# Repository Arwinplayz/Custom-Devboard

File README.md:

# Custom Devboard
A custom Devboard inspired by the Pico made in kicad
---

## Project Overview
The goal was to create a custom devboard PCB within kicad and learn how they truely work in the process.

This was one of my first projects I did so I truely learnt alot from it. Took some time off due to school and exams but finally managed to fint time to finish. Its multipurpose and fully programable GPIO pins so I look forward to using it alonside some other projects in the future. I decided overall to make this project because it would give me something really useful for future creations. Before this I had not a clue how microcontrollers and devboards worked but now I know so much.

---

## Screenshots

### 1. Overall

### 2. Schematic

### 3. PCB layout

### 4. Design

### Bill Of Materials

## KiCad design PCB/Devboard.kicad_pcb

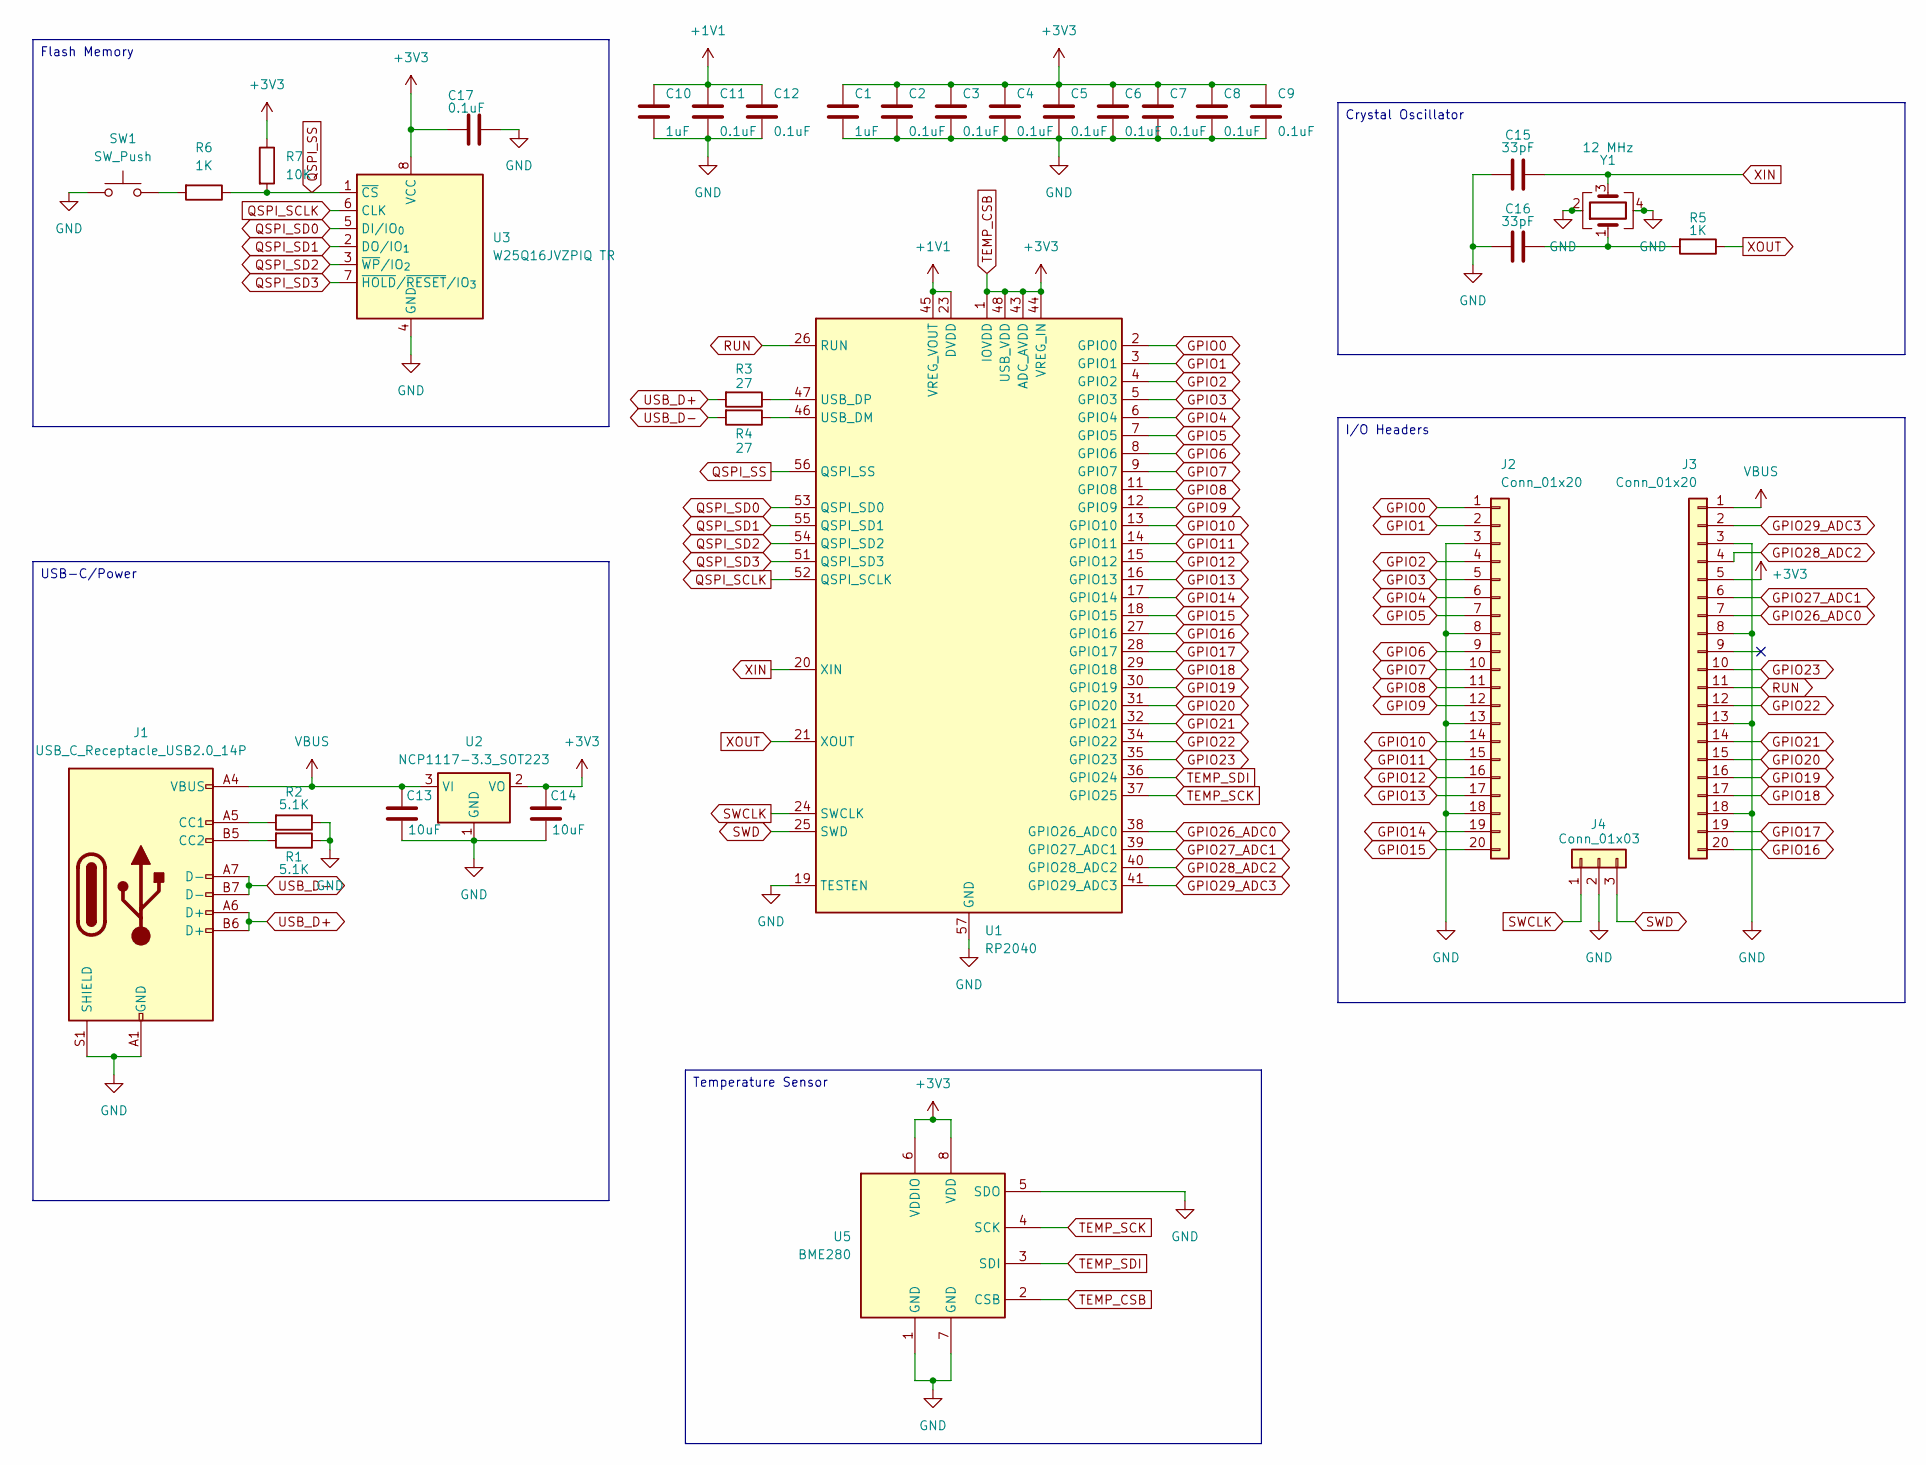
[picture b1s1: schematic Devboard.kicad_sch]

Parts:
C1, C10: 1uF; C_0402_1005Metric
C2, C3, C4, C5, C6, C7, C8, C9, C11, C12, C17: 0.1uF; C_0402_1005Metric
C13, C14: 10uF; C_0603_1608Metric
C15, C16: 33pF; C_0402_1005Metric
J1: USB_C_Receptacle_USB2.0_14P; USB_C_Receptacle_HRO_TYPE-C-31-M-12
J2, J3: Conn_01x20; PinHeader_1x20_P2.54mm_Vertical
J4: Conn_01x03; PinHeader_1x03_P2.54mm_Vertical
R1, R2: 5.1K; R_0402_1005Metric
R3, R4: 27; R_0402_1005Metric
R5, R6: 1K; R_0402_1005Metric
R7: 10K; R_0402_1005Metric
SW1: SW_Push; SW_Push_SPST_NO_Alps_SKRK
U1: RP2040; QFN-56-1EP_7x7mm_P0.4mm_EP3.2x3.2mm
U2: NCP1117-3.3_SOT223; SOT-23
U3: W25Q16JVZPIQ TR; Winbond_USON-8-1EP_3x2mm_P0.5mm_EP0.2x1.6mm
U5: BME280; Bosch_LGA-8_2.5x2.5mm_P0.65mm_ClockwisePinNumbering
Y1: 12 MHz; Crystal_SMD_3225-4Pin_3.2x2.5mm

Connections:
+1V1: C10.1, C11.1, C12.1, U1.23 (DVDD), U1.45 (VREG_VOUT), U1.50 (DVDD)
GND: C1.2, C2.2, C3.2, C4.2, C5.2, C6.2, C7.2, C8.2, C9.2, C10.2, C11.2, C12.2, C13.2, C14.2, C15.2, C16.2, C17.1, J1.A1 (GND), J1.A12 (GND), J1.B1 (GND), J1.B12 (GND), J1.S1 (SHIELD), J2.3, J2.8, J2.13, J2.18, J3.3, J3.8, J3.13, J3.18, J4.2, R1.1, R2.1, SW1.1, U1.19 (TESTEN), U1.57 (GND), U2.1 (GND), U3.4 (GND), U5.1 (GND), U5.5 (SDO), U5.7 (GND), Y1.2, Y1.4
GPIO0: J2.1, U1.2 (GPIO0)
GPIO1: J2.2, U1.3 (GPIO1)
GPIO2: J2.4, U1.4 (GPIO2)
GPIO3: J2.5, U1.5 (GPIO3)
GPIO4: J2.6, U1.6 (GPIO4)
GPIO5: J2.7, U1.7 (GPIO5)
GPIO6: J2.9, U1.8 (GPIO6)
GPIO7: J2.10, U1.9 (GPIO7)
GPIO8: J2.11, U1.11 (GPIO8)
GPIO9: J2.12, U1.12 (GPIO9)
GPIO10: J2.14, U1.13 (GPIO10)
GPIO11: J2.15, U1.14 (GPIO11)
GPIO12: J2.16, U1.15 (GPIO12)
GPIO13: J2.17, U1.16 (GPIO13)
GPIO14: J2.19, U1.17 (GPIO14)
GPIO15: J2.20, U1.18 (GPIO15)
GPIO16: J3.20, U1.27 (GPIO16)
GPIO17: J3.19, U1.28 (GPIO17)
GPIO18: J3.17, U1.29 (GPIO18)
GPIO19: J3.16, U1.30 (GPIO19)
GPIO20: J3.15, U1.31 (GPIO20)
GPIO21: J3.14, U1.32 (GPIO21)
GPIO22: J3.12, U1.34 (GPIO22)
GPIO23: J3.10, U1.35 (GPIO23)
GPIO26_ADC0: J3.7, U1.38 (GPIO26_ADC0)
GPIO27_ADC1: J3.6, U1.39 (GPIO27_ADC1)
GPIO28_ADC2: J3.4, U1.40 (GPIO28_ADC2)
GPIO29_ADC3: J3.2, U1.41 (GPIO29_ADC3)
unnamed: C16.1, R5.2, Y1.1
unnamed: J1.A5 (CC1), R2.2
unnamed: J1.B5 (CC2), R1.2
unnamed: R6.2, SW1.2
unnamed: R4.1, U1.46 (USB_DM)
unnamed: R3.1, U1.47 (USB_DP)
QSPI_SCLK: U1.52 (QSPI_SCLK), U3.6 (CLK)
QSPI_SD0: U1.53 (QSPI_SD0), U3.5 (DI/IO_{0})
QSPI_SD1: U1.55 (QSPI_SD1), U3.2 (DO/IO_{1})
QSPI_SD2: U1.54 (QSPI_SD2), U3.3 (~WP/IO_{2})
QSPI_SD3: U1.51 (QSPI_SD3), U3.7 (~HOLD/~RESET/IO_{3})
QSPI_SS: R6.1, R7.2, U1.56 (QSPI_SS), U3.1 (~CS)
RUN: J3.11, U1.26 (RUN)
SWCLK: J4.1, U1.24 (SWCLK)
SWD: J4.3, U1.25 (SWD)
TEMP_CSB: C1.1, C2.1, C3.1, C4.1, C5.1, C6.1, C7.1, C8.1, C9.1, C14.1, C17.2, J3.5, R7.1, U1.1 (IOVDD), U1.10 (IOVDD), U1.22 (IOVDD), U1.33 (IOVDD), U1.42 (IOVDD), U1.43 (ADC_AVDD), U1.44 (VREG_IN), U1.48 (USB_VDD), U1.49 (IOVDD), U2.2 (VO), U3.8 (VCC), U5.2 (CSB), U5.6 (VDDIO), U5.8 (VDD)
TEMP_SCK: U1.37 (GPIO25), U5.4 (SCK)
TEMP_SDI: U1.36 (GPIO24), U5.3 (SDI)
USB_D+: J1.A6 (D+), J1.B6 (D+), R3.2
USB_D-: J1.A7 (D-), J1.B7 (D-), R4.2
VBUS: C13.1, J1.A4 (VBUS), J1.A9 (VBUS), J1.B4 (VBUS), J1.B9 (VBUS), J3.1, U2.3 (VI)
XIN: C15.1, U1.20 (XIN), Y1.3
XOUT: R5.1, U1.21 (XOUT)

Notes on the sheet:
Flash Memory
Temperature Sensor
I/O Headers
Crystal Oscillator
USB-C/Power

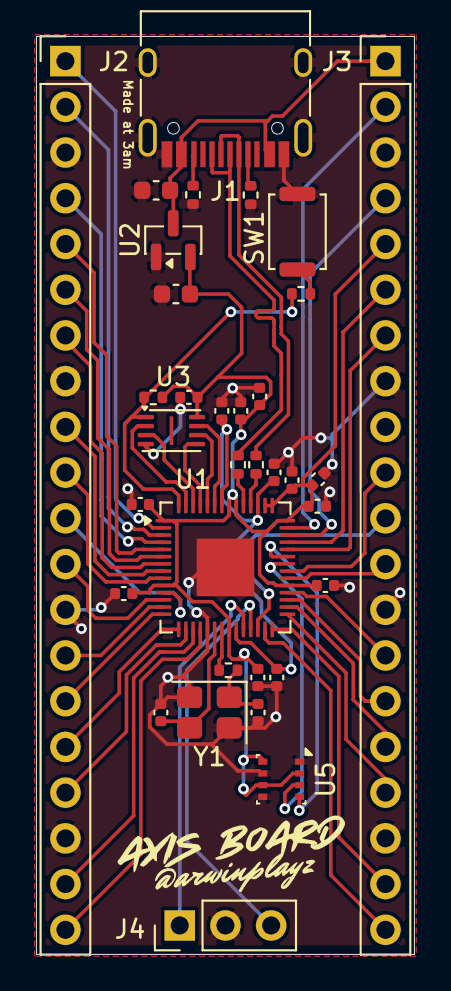
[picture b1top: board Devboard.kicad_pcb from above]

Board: 2 copper layers, 21.0 x 51.0 mm, 34 parts (0 on the bottom side), 53 nets.

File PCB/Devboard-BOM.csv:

Id,Designator,Footprint,Quantity,Comment,Supplier and ref
1,SW1,SW_Push_SPST_NO_Alps_SKRK,1,SW_Push,
2,U2,SOT-23,1,NCP1117-3.3_SOT223,
3,"C6,C3,C8,C17,C12,C7,C4,C11,C5,C9,C2",C_0402_1005Metric,11,0.1uF,
4,J1,USB_C_Receptacle_HRO_TYPE-C-31-M-12,1,USB_C_Receptacle_USB2.0_14P,
5,U1,QFN-56-1EP_7x7mm_P0.4mm_EP3.2x3.2mm,1,RP2040,
6,"C1,C10",C_0402_1005Metric,2,1uF,
7,"R6,R5",R_0402_1005Metric,2,1K,
8,"C14,C13",C_0603_1608Metric,2,10uF,
9,R7,R_0402_1005Metric,1,10K,
10,"R2,R1",R_0402_1005Metric,2,5.1K,
11,"R3,R4",R_0402_1005Metric,2,27,
12,U3,Winbond_USON-8-1EP_3x2mm_P0.5mm_EP0.2x1.6mm,1,W25Q16JVZPIQ TR,
13,Y1,Crystal_SMD_3225-4Pin_3.2x2.5mm,1,12 MHz,
14,"J3,J2",PinHeader_1x20_P2.54mm_Vertical,2,Conn_01x20,
15,"C15,C16",C_0402_1005Metric,2,33pF,
16,J4,PinHeader_1x03_P2.54mm_Vertical,1,Conn_01x03,

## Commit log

2025-12-19 added local files
2025-12-19 Create README.md with project details and images
    Added project overview, screenshots, and BOM.
2025-12-19 added images
2025-12-19 added bom image
2026-01-07 added temperature sensor
2026-01-07 fixed image size
2026-03-22 Enhance README
    Expanded project overview with personal insights and experiences.
2026-03-22 updated images
2026-03-22 updated bom
2026-03-22 changed temperature sensor
